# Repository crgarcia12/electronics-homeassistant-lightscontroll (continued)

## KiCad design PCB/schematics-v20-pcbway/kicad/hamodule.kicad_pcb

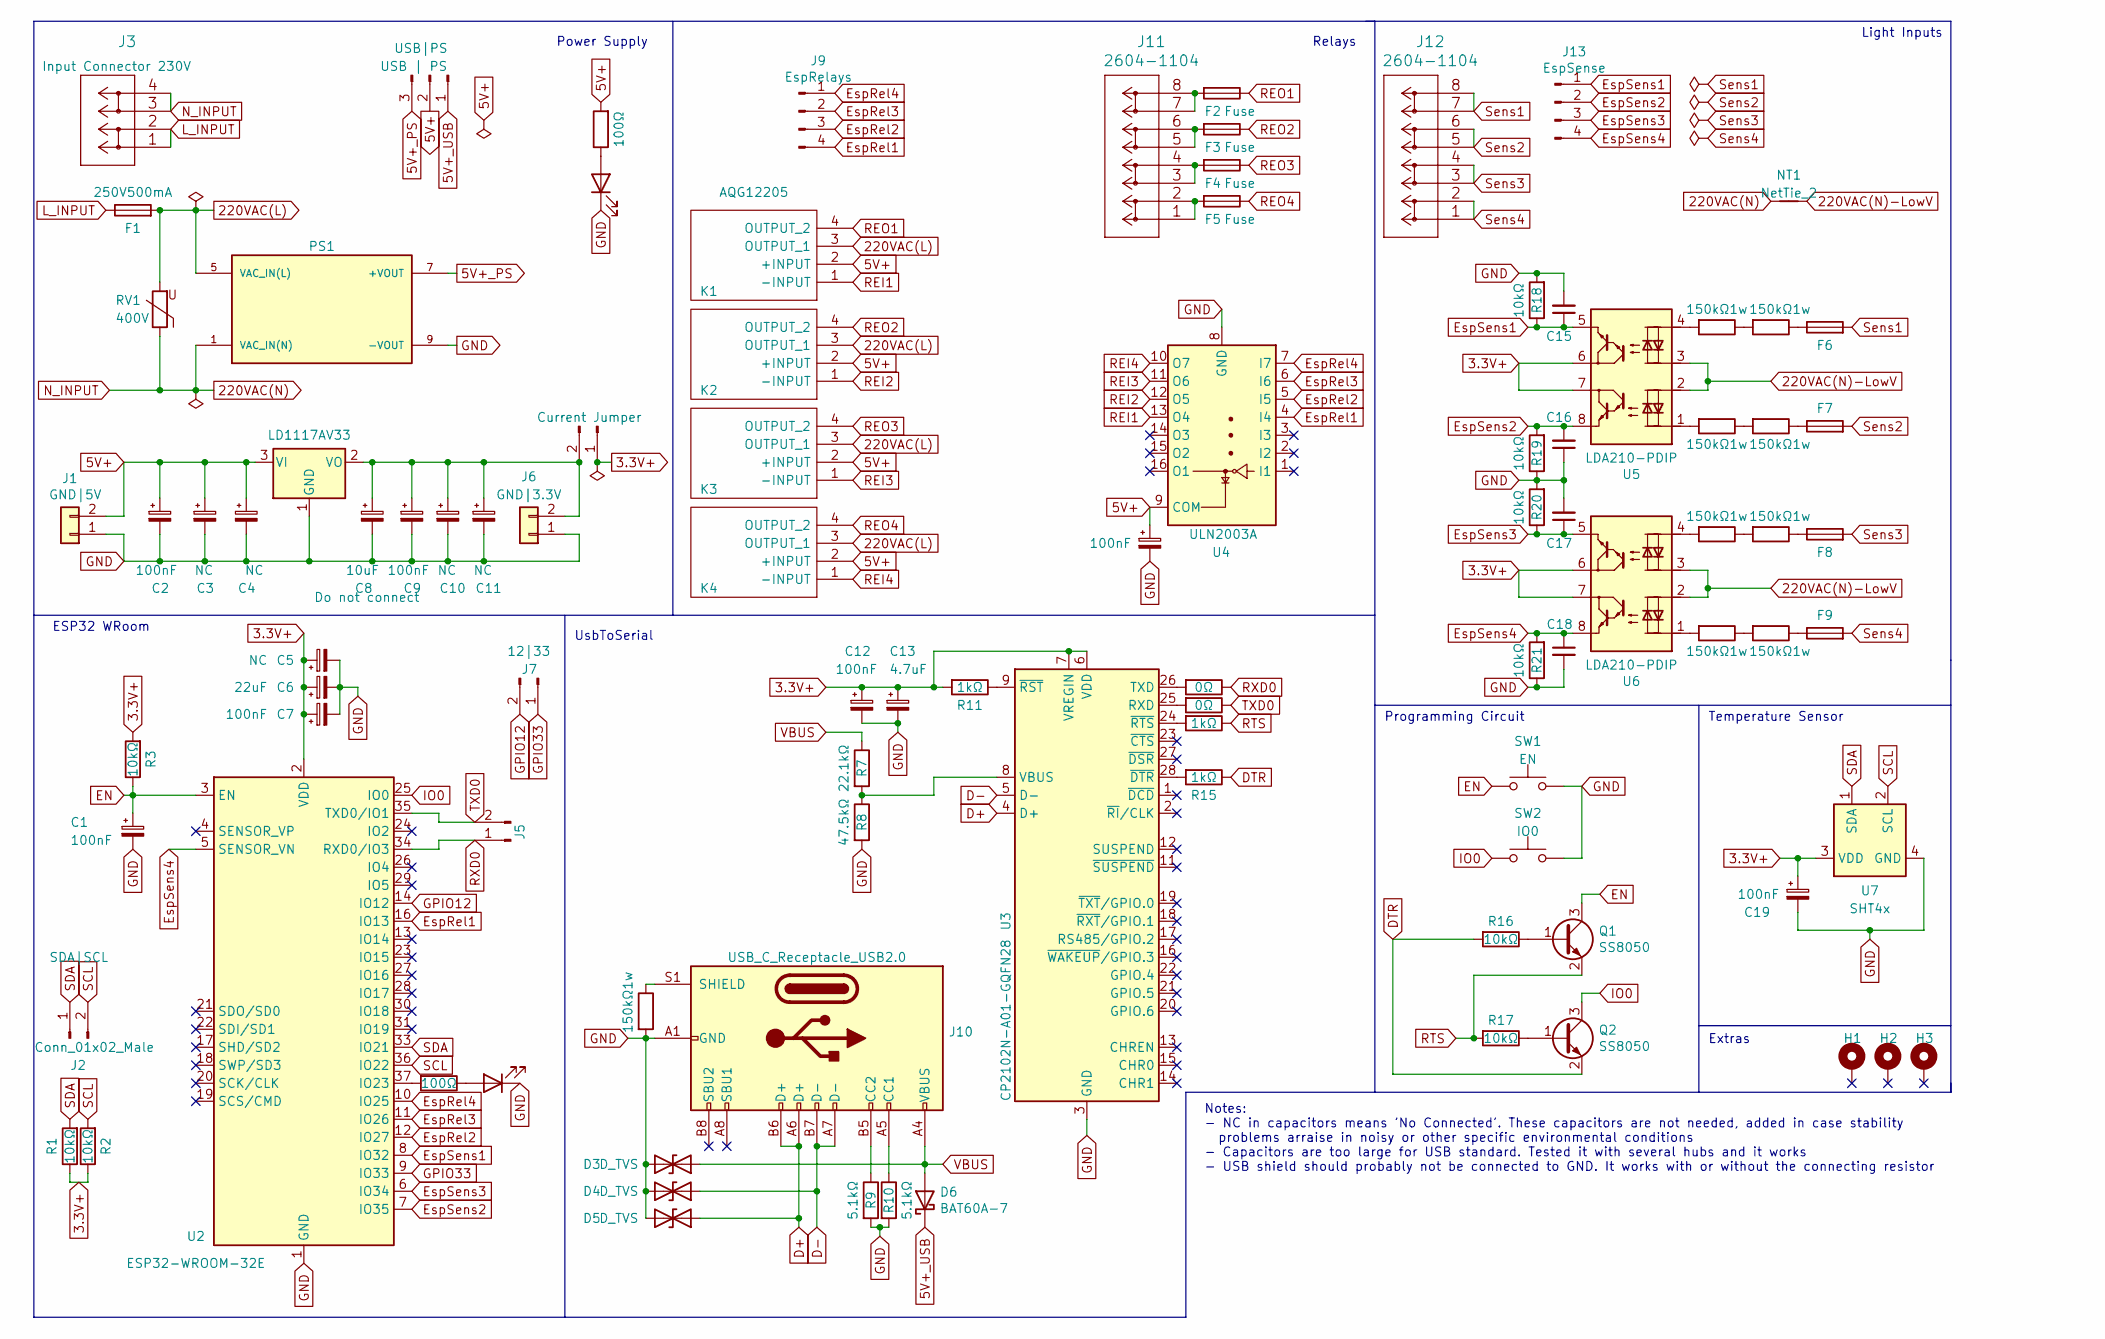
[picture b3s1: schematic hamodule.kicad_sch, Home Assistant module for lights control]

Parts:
C1, C2, C7, C9, C12, C14, C19: 100nF; C_0603_1608Metric_Pad1.08x0.95mm_HandSolder; JLCPCB C14663
C3, C4, C10, C11: NC; C_0805_2012Metric_Pad1.18x1.45mm_HandSolder
C5: NC; C_0603_1608Metric_Pad1.08x0.95mm_HandSolder
C6, C15, C16, C17, C18: 22uF; C_0603_1608Metric_Pad1.08x0.95mm_HandSolder; JLCPCB C59461
C8: 10uF; CP_Radial_D6.3mm_P2.50mm
C13: 4.7uF; C_0603_1608Metric_Pad1.08x0.95mm_HandSolder; JLCPCB C19666
D1, D2: LED; LED_0805_2012Metric_Pad1.15x1.40mm_HandSolder; JLCPCB C2297
D3, D4, D5: D_TVS; D_SOD-523; JLCPCB C383211
D6: BAT60A-7; D_SOD-323; JLCPCB C124187
F1: 250V500mA; Fuseholder_TR5_Littelfuse_No560_No460
F2, F3, F4, F5, F6, F7, F8, F9: Fuse; FUSE_RST-1-BULK
H1, H2, H3: MountingHole_Pad; MountingHole_3.2mm_M3_ISO14580_Pad
J1: GND|5V; JST_XH_B2B-XH-A_1x02_P2.50mm_Vertical
J2, J5, J7: Conn_01x02_Male; PinHeader_1x02_P2.54mm_Vertical
J3: 2604-1102; big_pads_2604-1102
J4: USB | PS; PinHeader_1x03_P2.54mm_Vertical
J6: GND|3.3V; JST_XH_B2B-XH-A_1x02_P2.50mm_Vertical
J8: Current Jumper; PinHeader_1x02_P2.54mm_Vertical
J9: EspRelays; PinSocket_1x04_P2.54mm_Vertical
J10: USB_C_Receptacle_USB2.0; USB_C_Receptacle_HRO_TYPE-C-31-M-12; JLCPCB C167321
J11, J12: 2604-1104; big_pads_2604-1104
J13: EspSense; PinSocket_1x04_P2.54mm_Vertical
K1, K2, K3, K4: AQG12205; Manufacturer_Part_Number AQG12205; Mouser Part Number 769-AQG12205
NT1: NetTie_2; NetTie-2_SMD_Pad2.0mm
PS1: RAC05-05SK/277; 277; PARTREV N/A
Q1, Q2: SS8050; SOT-23; JLCPCB C177739
R1, R2, R3, R16, R17, R18, R19, R20, R21: 10kΩ; R_0603_1608Metric_Pad0.98x0.95mm_HandSolder; JLCPCB C25804
R4, R5: 100Ω; R_0805_2012Metric_Pad1.20x1.40mm_HandSolder; JLCPCB C17408
R6, R22, R23, R24, R25, R26, R27, R28, R29: 150kΩ1w; R_2512_6332Metric_Pad1.40x3.35mm_HandSolder; JLCPCB C25719
R7: 22.1kΩ; R_0603_1608Metric_Pad0.98x0.95mm_HandSolder; JLCPCB C25961
R8: 47.5kΩ; R_0603_1608Metric_Pad0.98x0.95mm_HandSolder; JLCPCB C23061
R9, R10: 5.1kΩ; R_0603_1608Metric_Pad0.98x0.95mm_HandSolder; JLCPCB C23186
R11, R15: 1kΩ; R_0603_1608Metric_Pad0.98x0.95mm_HandSolder; JLCPCB C25585
R12, R13: 0Ω; R_0805_2012Metric_Pad1.20x1.40mm_HandSolder; JLCPCB C17477
R14: 1kΩ; R_1206_3216Metric_Pad1.30x1.75mm_HandSolder; JLCPCB C4410
RV1: 400V; RV_Disc_D12mm_W4.2mm_P7.5mm
SW1, SW2: Switch; SW_SPST_SKQG_WithStem; JLCPCB C318884
U1: LD1117AV33; TO-220-3_Vertical
U2: ESP32-WROOM-32E; ESP32-WROOM-32; JLCPCB C701343
U3: CP2102N-A01-GQFN28; QFN-28-1EP_5x5mm_P0.5mm_EP3.35x3.35mm; JLCPCB C964632
U4: ULN2003A; SOIC-16_3.9x9.9mm_P1.27mm; JLCPCB C7512
U5, U6: LDA210-PDIP; DIP-8_W7.62mm_Socket_LongPads
U7: SHT4x; XDCR_SHT40-AD1B-R2; JLCPCB C2909890

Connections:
3.3V+: C5.1, C6.1, C7.1, C12.1, C13.1, C19.1, J8.1, R1.1, R2.1, R3.2, R11.2, U2.2 (VDD), U3.6 (VDD), U3.7 (VREGIN), U5.6, U5.7, U6.6, U6.7, U7.3 (VDD)
5V+: C2.1, C3.1, C4.1, C14.1, J1.2, J4.2, K1.2 (+INPUT), K2.2 (+INPUT), K3.2 (+INPUT), K4.2 (+INPUT), R5.2, U1.3 (VI), U4.9 (COM)
5V+_PS: J4.3, PS1.7 (+VOUT)
5V+_USB: D6.1 (K), J4.1
220VAC(L): F1.2, K1.3 (OUTPUT_1), K2.3 (OUTPUT_1), K3.3 (OUTPUT_1), K4.3 (OUTPUT_1), PS1.5 (VAC_IN(L)), RV1.2
220VAC(N): J3.3, J3.4, NT1.1, PS1.1 (VAC_IN(N)), RV1.1
220VAC(N)-LowV: NT1.2, U5.2, U5.3, U6.2, U6.3
D+: D5.1 (A1), J10.A6 (D+), J10.B6 (D+), U3.4 (D+)
D-: D4.1 (A1), J10.A7 (D-), J10.B7 (D-), U3.5 (D-)
DTR: Q2.2 (E), R15.1, R16.2
EN: C1.1, Q1.3 (C), R3.1, SW1.1, U2.3 (EN)
EspRel1: J9.4, U2.16 (IO13), U4.4 (I4)
EspRel2: J9.3, U2.12 (IO27), U4.5 (I5)
EspRel3: J9.2, U2.11 (IO26), U4.6 (I6)
EspRel4: J9.1, U2.10 (IO25), U4.7 (I7)
EspSens1: C15.1, J13.1, R18.1, U2.8 (IO32), U5.5
EspSens2: C16.2, J13.2, R19.2, U2.7 (IO35), U5.8
EspSens3: C17.1, J13.3, R20.1, U2.6 (IO34), U6.5
EspSens4: C18.1, J13.4, R21.2, U2.5 (SENSOR_VN), U6.8
GND: C1.2, C2.2, C3.2, C4.2, C5.2, C6.2, C7.2, C8.2, C9.2, C10.2, C11.2, C12.2, C13.2, C14.2, C15.2, C16.1, C17.2, C18.2, C19.2, D1.1 (K), D2.1 (K), D3.2 (A2), D4.2 (A2), D5.2 (A2), J1.1, J6.1, J10.A1 (GND), J10.A12 (GND), J10.B1 (GND), J10.B12 (GND), PS1.9 (-VOUT), R6.2, R8.2, R9.2, R10.2, R18.2, R19.1, R20.2, R21.1, SW1.2, SW2.2, U1.1 (GND), U2.1 (GND), U2.15 (GND), U2.38 (GND), U2.39 (GND), U3.3 (GND), U3.29 (GND), U4.8 (GND), U7.4 (GND)
GPIO12: J7.2, U2.14 (IO12)
GPIO33: J7.1, U2.9 (IO33)
IO0: Q2.3 (C), SW2.1, U2.25 (IO0)
L_INPUT: F1.1, J3.1, J3.2
unnamed: C8.1, C9.1, C10.1, C11.1, J6.2, J8.2, U1.2 (VO)
unnamed: D1.2 (A), R4.1
unnamed: D2.2 (A), R5.1
unnamed: F2.2, J11.7, J11.8
unnamed: F3.2, J11.5, J11.6
unnamed: F4.2, J11.3, J11.4
unnamed: F5.2, J11.1, J11.2
unnamed: F6.1, R26.1
unnamed: F7.1, R27.1
unnamed: F8.1, R28.1
unnamed: F9.1, R29.1
unnamed: J10.A5 (CC1), R10.1
unnamed: J10.B5 (CC2), R9.1
unnamed: J10.S1 (SHIELD), R6.1
unnamed: Q1.1 (B), R16.1
unnamed: Q2.1 (B), R17.1
unnamed: R4.2, U2.37 (IO23)
unnamed: R7.2, R8.1, U3.8 (VBUS)
unnamed: R11.1, U3.9 (~RST)
unnamed: R12.2, U3.26 (TXD)
unnamed: R13.2, U3.25 (RXD)
unnamed: R14.2, U3.24 (~RTS)
unnamed: R15.2, U3.28 (~DTR)
unnamed: R22.1, R26.2
unnamed: R22.2, U5.4
unnamed: R23.1, R27.2
unnamed: R23.2, U5.1
unnamed: R24.1, R28.2
unnamed: R24.2, U6.4
unnamed: R25.1, R29.2
unnamed: R25.2, U6.1
REI1: K1.1 (-INPUT), U4.13 (O4)
REI2: K2.1 (-INPUT), U4.12 (O5)
REI3: K3.1 (-INPUT), U4.11 (O6)
REI4: K4.1 (-INPUT), U4.10 (O7)
REO1: F2.1, K1.4 (OUTPUT_2)
REO2: F3.1, K2.4 (OUTPUT_2)
REO3: F4.1, K3.4 (OUTPUT_2)
REO4: F5.1, K4.4 (OUTPUT_2)
RTS: Q1.2 (E), R14.1, R17.2
RXD0: J5.1, R12.1, U2.34 (RXD0/IO3)
SCL: J2.2, R2.2, U2.36 (IO22), U7.2 (SCL)
SDA: J2.1, R1.2, U2.33 (IO21), U7.1 (SDA)
Sens1: F6.2, J12.7, J12.8
Sens2: F7.2, J12.5, J12.6
Sens3: F8.2, J12.3, J12.4
Sens4: F9.2, J12.1, J12.2
TXD0: J5.2, R13.1, U2.35 (TXD0/IO1)
VBUS: D3.1 (A1), D6.2 (A), J10.A4 (VBUS), J10.A9 (VBUS), J10.B4 (VBUS), J10.B9 (VBUS), R7.1

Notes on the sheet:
Programming Circuit
UsbToSerial
Relays
Temperature Sensor
Power Supply
Extras
ESP32 WRoom
Notes: - NC in capacitors means 'No Connected'. These capacitors are not needed, added in case stability problems arraise in noisy or other specific environmental conditions - Capacitors are too large for USB standard. Tested it with several hubs and it works - USB shield should probably not be con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
Light Inputs

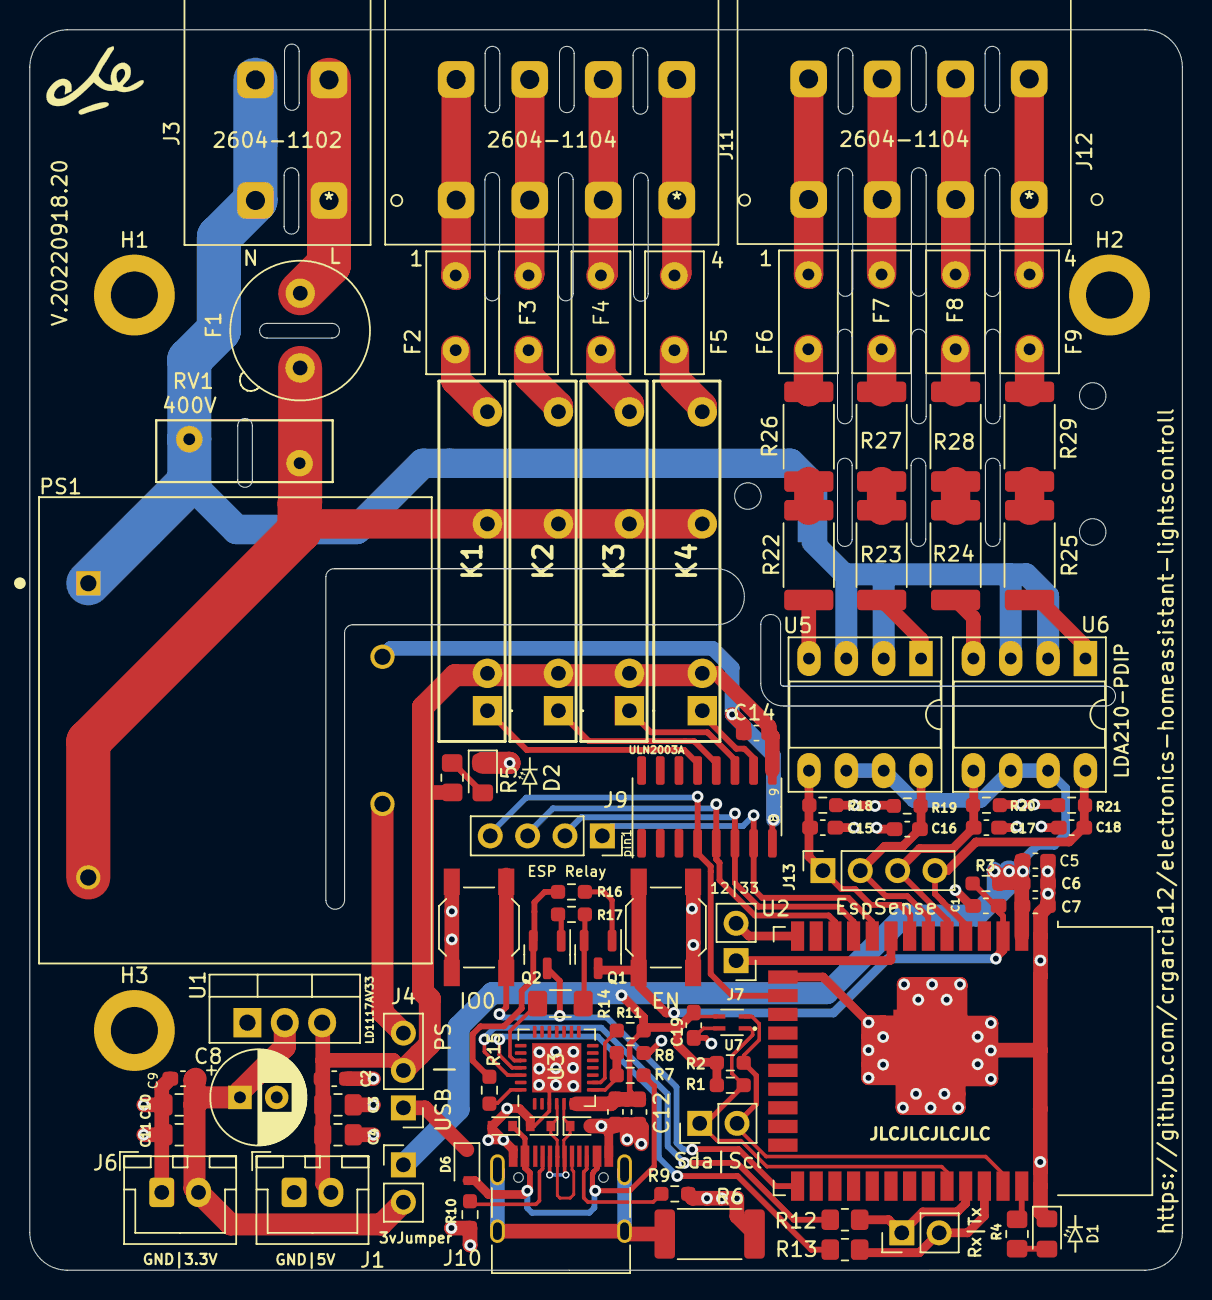
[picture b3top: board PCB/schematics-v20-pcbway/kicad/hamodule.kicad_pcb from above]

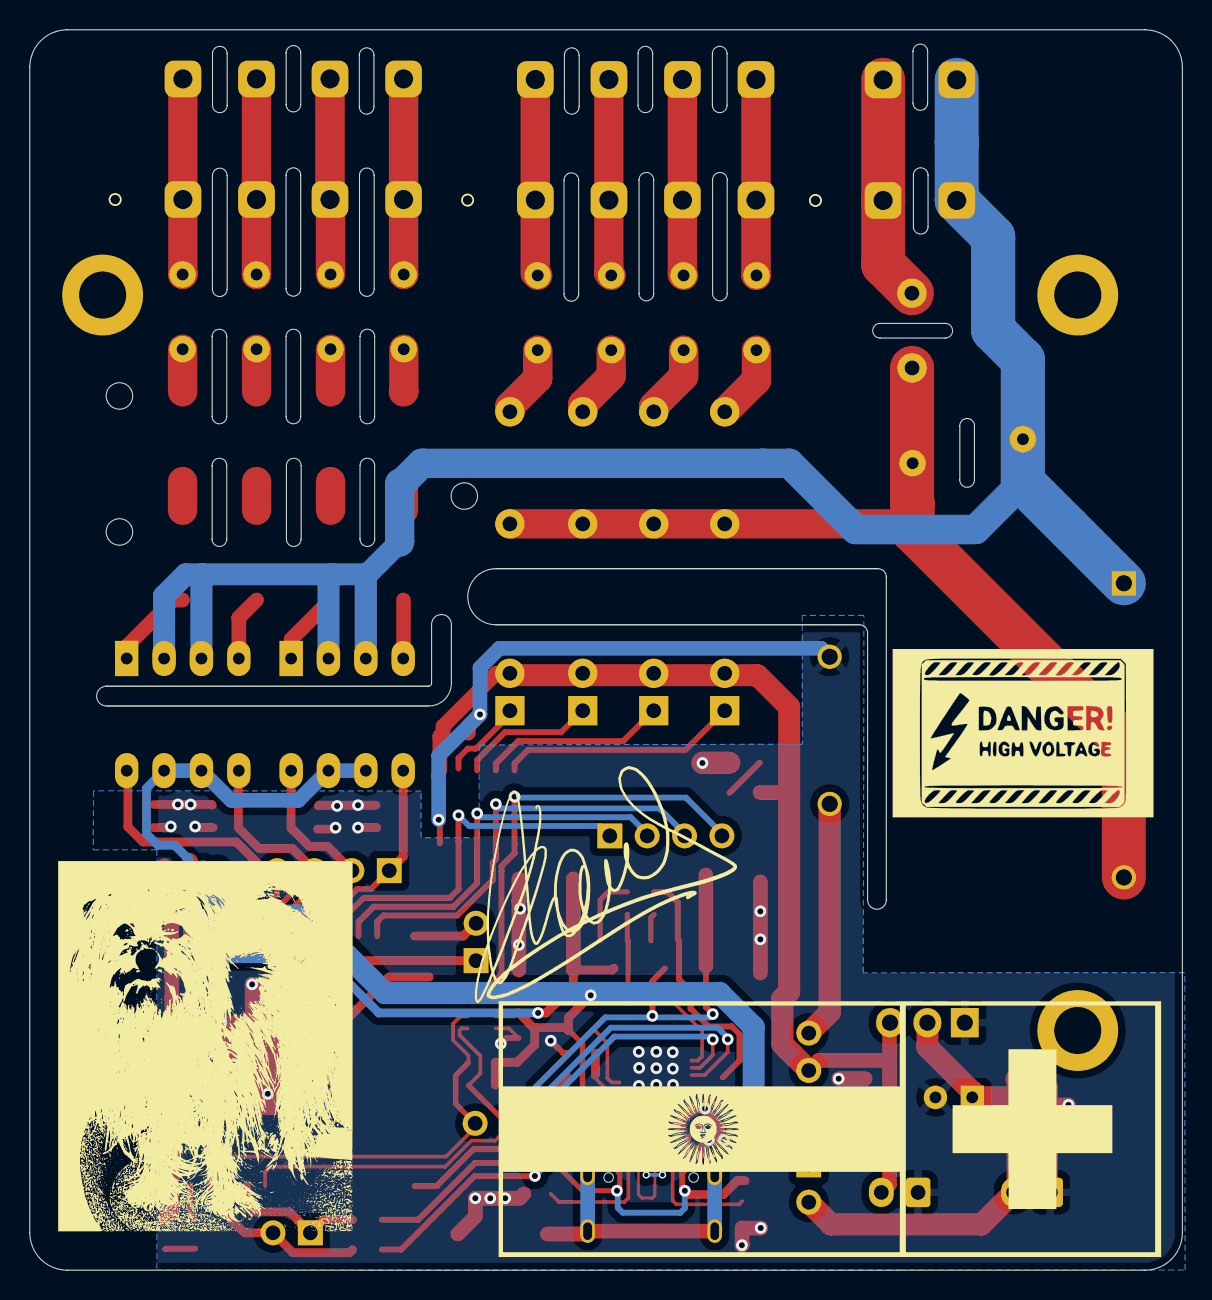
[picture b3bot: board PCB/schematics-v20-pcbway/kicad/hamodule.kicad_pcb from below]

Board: 2 copper layers, 78.4 x 84.3 mm, 104 parts (5 on the bottom side), 73 nets.

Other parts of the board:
G1: LOGO; che
G2, G4: LOGO; led_6000dpi
G3: LOGO; danger1_negative
G5: LOGO; depsi
G6: LOGO; flags
G7: LOGO; paula
